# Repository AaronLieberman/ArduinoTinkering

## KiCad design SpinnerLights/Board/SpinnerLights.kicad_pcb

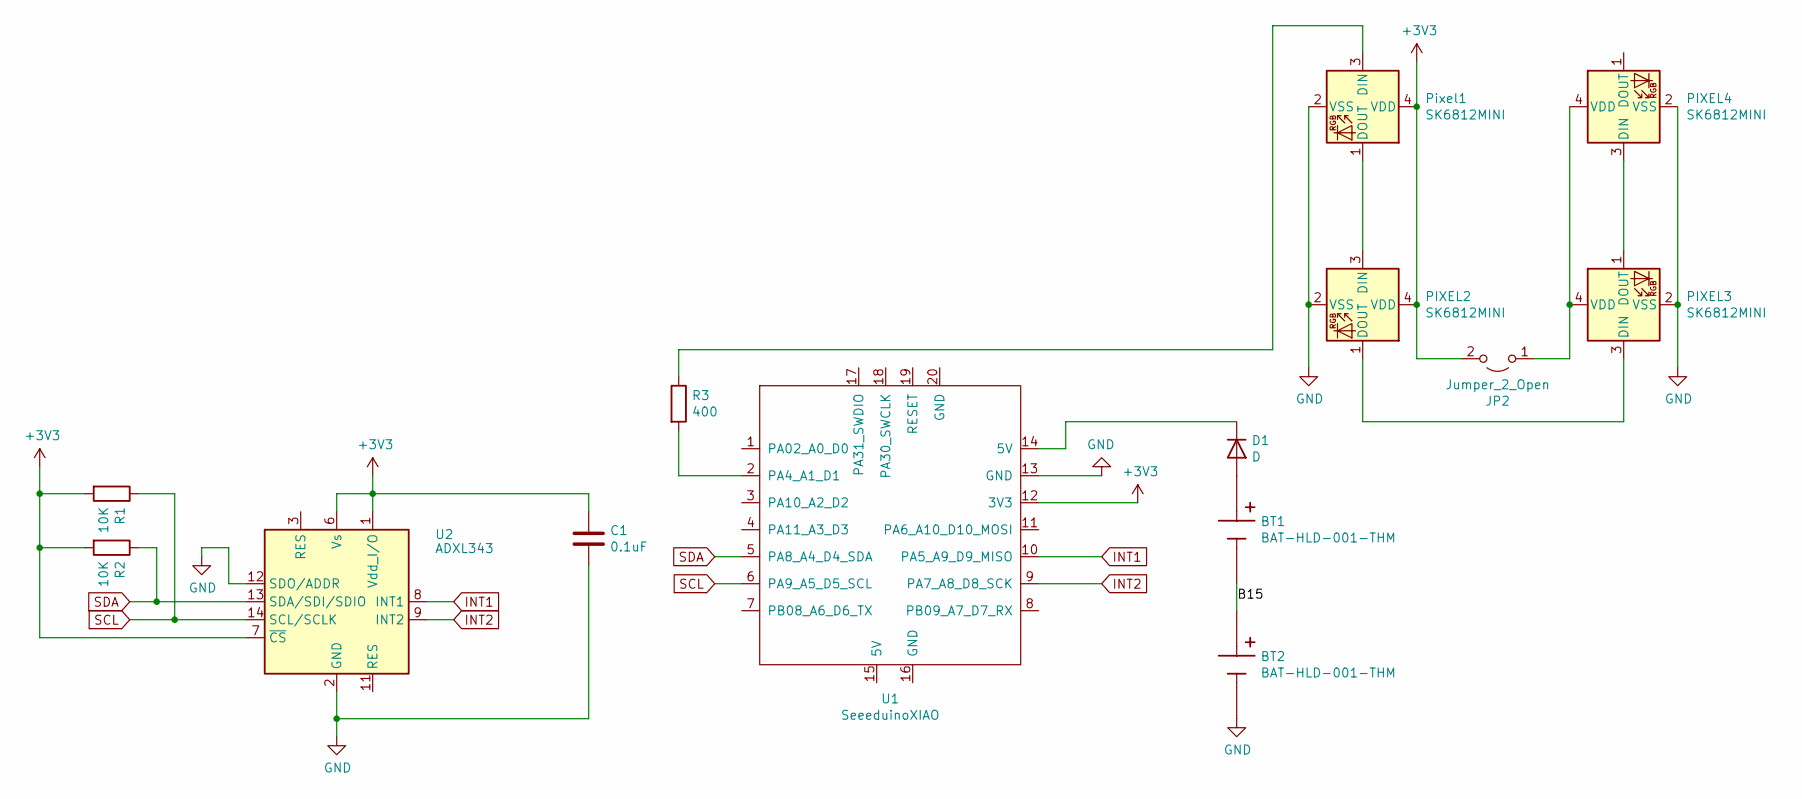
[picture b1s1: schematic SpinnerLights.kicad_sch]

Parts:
BT1, BT2: BAT-HLD-001-THM; BAT_BAT-HLD-001-THM; PARTREV C
C1: 0.1uF; C_0805_2012Metric
D1: D; D_SOD-323
JP2: Jumper_2_Open; SolderJumper-2_P1.3mm_Open_RoundedPad1.0x1.5mm
PIXEL2, PIXEL3, PIXEL4: SK6812MINI; LED_SK6812MINI_PLCC4_3.5x3.5mm_P1.75mm
Pixel1: SK6812MINI; LED_SK6812MINI_PLCC4_3.5x3.5mm_P1.75mm
R1, R2: 10K; R_0805_2012Metric_Pad1.20x1.40mm_HandSolder
R3: 400; R_0805_2012Metric_Pad1.20x1.40mm_HandSolder
U1: SeeeduinoXIAO; Seeeduino XIAO-MOUDLE14P-2.54-21X17.8MM
U2: ADXL343; LGA-14_3x5mm_P0.8mm_LayoutBorder1x6y

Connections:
+3V3: C1.1, JP2.2 (B), PIXEL2.4 (VDD), Pixel1.4 (VDD), R1.2, R2.2, U1.12 (3V3), U2.1 (Vdd_I/O), U2.6 (Vs), U2.7 (~CS)
/B15: BT1.N, BT2.P1, BT2.P2, BT2.P3, BT2.P4
GND: BT2.N, C1.2, PIXEL2.2 (VSS), PIXEL3.2 (VSS), PIXEL4.2 (VSS), Pixel1.2 (VSS), U1.13 (GND), U2.2 (GND), U2.4 (GND), U2.5 (GND), U2.12 (SDO/ADDR)
INT1: U1.10 (PA5_A9_D9_MISO), U2.8 (INT1)
INT2: U1.9 (PA7_A8_D8_SCK), U2.9 (INT2)
unnamed: BT1.P1, BT1.P2, BT1.P3, BT1.P4, D1.2 (A)
unnamed: D1.1 (K), U1.14 (5V)
unnamed: JP2.1 (A), PIXEL3.4 (VDD), PIXEL4.4 (VDD)
unnamed: PIXEL2.1 (DOUT), PIXEL3.3 (DIN)
unnamed: PIXEL2.3 (DIN), Pixel1.1 (DOUT)
unnamed: PIXEL3.1 (DOUT), PIXEL4.3 (DIN)
unnamed: Pixel1.3 (DIN), R3.1
unnamed: R3.2, U1.2 (PA4_A1_D1)
SCL: R1.1, U1.6 (PA9_A5_D5_SCL), U2.14 (SCL/SCLK)
SDA: R2.1, U1.5 (PA8_A4_D4_SDA), U2.13 (SDA/SDI/SDIO)

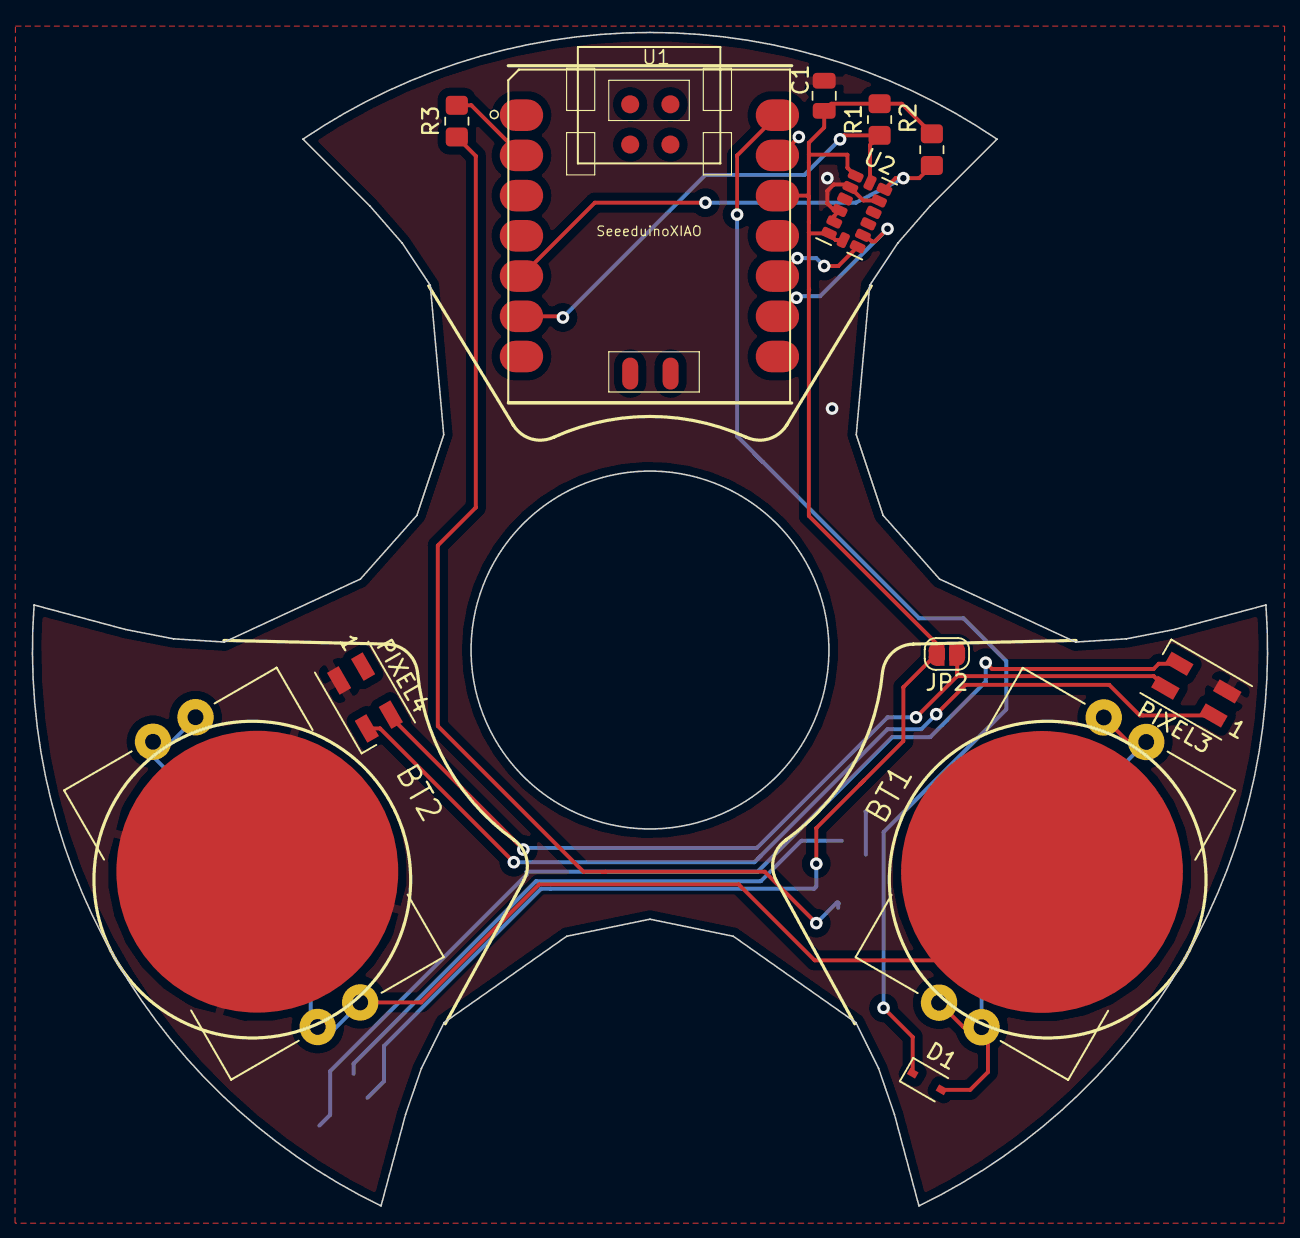
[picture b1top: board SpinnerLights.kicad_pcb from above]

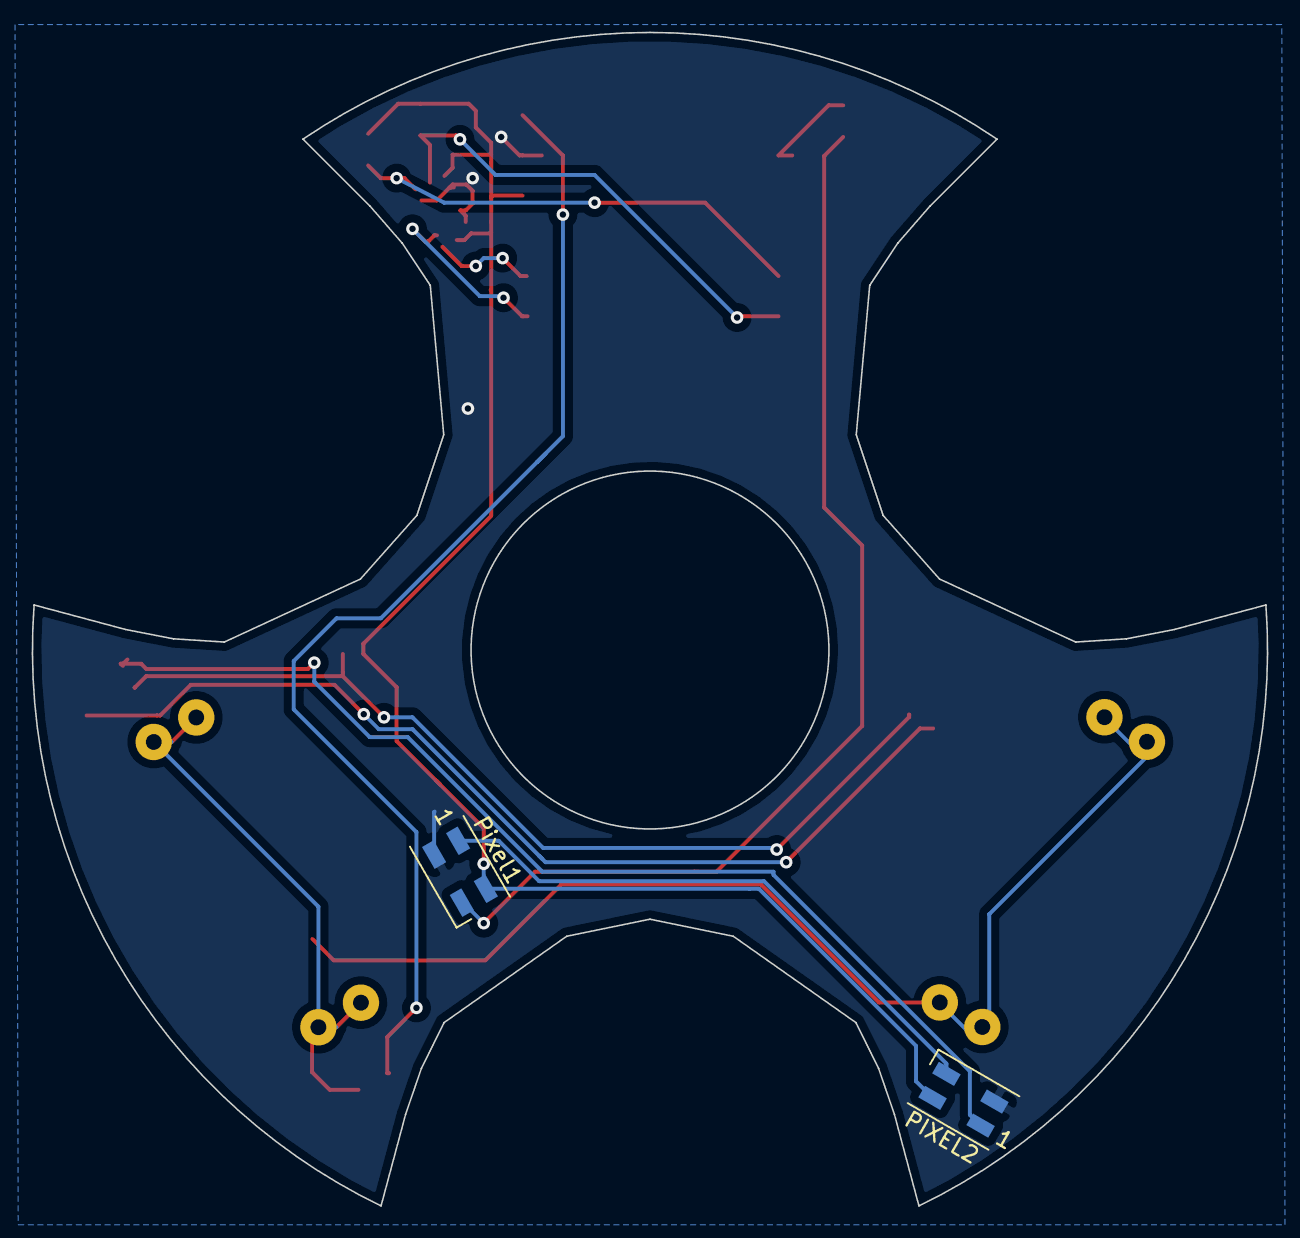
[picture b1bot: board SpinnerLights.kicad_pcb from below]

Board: 2 copper layers, 78.0 x 74.1 mm, 14 parts (2 on the bottom side), 15 nets.

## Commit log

2015-08-01 Added Temperature
2015-08-01 Added LedDisplay
2015-08-16 updates for new board layout, wip debugging stuff
2015-08-16 initial temperaturedisplay checkin
2015-08-16 minor cleanup and rename of variables
2015-08-17 Getting updated to the final layout of the trinket pro board. Extract various classes out to make TemperatureDisplay.
2015-08-17 Initial check-in of Thermostat by copying Temperatore
2015-08-17 V1 complete!
2016-01-10 led display no longer flickers! interrupts ftw
2016-01-10 tiny bit of code cleanup
2016-01-26 initial soundfabric checkin. controls the hue of several neopixels
2016-01-27 up to 7 pixels, add brightness wave
2016-01-28 whitespace fix
2016-01-28 add hue shift graph jpg for later reference
2016-01-29 mic controls a led strand
2016-01-30 continuous brightness based on volume
2016-01-30 Split out NeoPixelHue to it's own directory
2016-01-30 Add gain and log scale. It's working! Mic is picking up the sound and displaying it on the pixels.
2016-01-31 FHT Test
2016-01-31 getting slightly closer to fht but its still not working
2016-02-01 add .gitignore
2016-02-01 fftvisualizer windows app
2016-02-01 cleanup fftvisualizer code
2016-02-01 Visualization achievied!
2016-02-01 FhtToSerialTest app
2016-04-07 Add FFTVisualizer sketch and C# serial over USB app
2016-04-07 Revert "Add FFTVisualizer sketch and C# serial over USB app"
    This reverts commit 1848aa800e20f29074f41e0ccba744a692173c60.
2016-04-07 improvements to FFTVisualizer
2016-04-09 add micserial and visualizer
2016-05-04 FFTTest Python app, trying to figure out how FFT works.
2016-05-04 add .vc.db (python related VS file?) to .gitignore
2016-05-08 make data path relative
2016-05-30 working spectrum analyzer
2016-05-30 plays the right number of samples/s
2016-05-30 remove some commented out code
2016-06-02 add python version file
2016-06-02 make a copies of ffttest2.py for win and pi
2016-06-03 update FFTTest2-pi to use curses correctly
2016-06-04 add draft of alssound
2016-06-04 draft of using alsaudio
2016-06-04 add accidentally removed curses stuff back in
2016-10-09 fix NeoPixelHue delay
2016-10-09 fix temperature, should be targetting 150
2016-10-09 Halloween lights project
2017-01-06 Simple Fireflies blinking lights sketch
2017-01-06 Simple sketch to blink neopixels for halloween
2017-01-08 7 neopixel fireflies
2017-01-08 add lifetime scaling via pot
2017-01-22 Light detector using LEDs
2017-01-22 Fireflies - at least one LED is always on
2017-01-22 rename loop to tick
2017-01-22 Add some comments on how to use, rename some vars
2017-01-22 - Re-add loop, was inadvertently removed - Add second pixel strand, currently only has one pixel in it
2017-02-16 update fireflies to use fairy lights
2018-04-10 random changes from who knows when
2018-04-10 circuit playground express docs
2018-06-09 Get up and running in VS Code. Files for Trinket M0.
2018-06-09 Add ShelfLights.ino
2018-06-09 clang format
2018-12-30 remove .vscode dir from repo
2018-12-30 final version for shelflights
2019-01-02 Initial RobotController app
2019-01-02 Update to package references, switch to Addle version of Core and WPF
2019-01-02 Add message received UI
2019-01-04 RobotControl w/ SerialPort replacement class that actually works (unlike the built in .NET one)
2019-01-06 Robot controller works!
2019-01-19 minor tweak
2019-02-14 messing with robot control via python and arduino
2019-02-16 start code to load animations.txt
2019-03-13 animation playback software
2019-03-14 per-servo config
2019-03-27 Animations finally working!
2019-04-11 LED buttons work! - Fix stlhelper to work for multiple files
2019-04-13 buttons to trigger animations
2019-05-05 initial OzControlPanel check in + try out scheduler library
2019-05-08 v1.0
2019-05-21 final oz
2019-06-19 minor adjustments to enable_servos define
2019-06-19 New animationData
2019-06-19 robot blender file
2019-07-31 Initial MalStaff
2019-08-03 glow and blinking green
2019-08-11 might be the final version of the staff
2019-09-28 add clang format for RobotAnimations
2019-09-28 Clang format RobotAnimations
2019-09-28 Extract out ServoController
2019-09-29 doesn't crash anymore, ready for dev again
2019-09-29 Extract out AnimationPlayer
2019-09-29 setup mode works
2019-09-29 wave working
2019-09-30 animations work
2019-09-30 Fixed data to be correctly const so it lives in flash instead of sram
2019-09-30 update blend files
2019-10-04 Pretty much final software
2019-10-04 update animations
2019-10-04 more work on the macerena
2019-10-04 maybe done now?
2019-10-04 macerena blend file
2019-10-04 adjust idle timeout
2019-12-22 VolumeControl
2019-12-22 comment
2019-12-23 better button support
2019-12-23 switch encoder to use polling instead of interrupts
2019-12-23 simplify encoder logic
2019-12-24 move where serial is initialized
2020-07-26 PrusaLights
2020-07-26 VS Code workspace
2020-09-05 Update default clang format to use attached braces
2020-09-05 more clang format updates
2020-09-05 Beginning of HyperFig code
2020-09-05 Add some of the .vscode files to source control
2020-09-07 HyperFig code complete
2021-08-23 HyperFig: some progress towards multiple buttons on one pin
    also some line endings fixing i think
2021-08-23 Initial SpinnerLights (copied from HyperFig)
2021-08-23 SpinnerLights controls NeoPixels
2021-08-24 SpinnerLights: uses accelerometer on PyBadge to control neopixels
2021-08-28 Filter accel values, a bit of cleanup
2021-08-28 A little header cleanup
2021-10-12 Basic spinner works
2021-10-12 clangformat: fix pointer alignment
2021-10-12 Move SpinnerLights to subdir
2021-10-12 SpinnerLights: Initial KiCad setup
2021-10-13 WIP on SpinnerLights board
2021-10-13 SpinnerLights: Initial netlist and schematics
2021-10-13 SpinnerLights: Initial board generation
2021-10-13 SpinnerLights: More progress on board layout
2021-10-14 SpinnerLights: started laying down wires
2021-10-14 SpinnerLights: Almost complete routing
2021-10-14 SpinnerLights: Initial version first pass complete
2021-10-14 SpinnerLights: Fix I2C interface pins
2021-10-14 SpinnerLights: minor tweaks to ground plane
2021-10-15 SpinnerLights: Rename a couple nets
2021-10-15 SpinnerLights: Fix symbols for NeoPixels
2021-10-15 SpinnerLights: move a couple of components around to give more space
2021-10-16 SpinnerLights: Minor tweaks to placement and routing
2021-10-16 SpinnerLights: Remove files that don't belong in source control
2021-10-16 SpinnerLights: .gitignore file
2022-01-09 Upgrade kicad files to v6
2022-05-18 Get SpinnerLights to build again by moving to directory named SpinnerLights
2022-05-18 SpinnerLights: Get working with PCB version and ADXL345
2022-05-20 PCB v1 complete
2022-09-22 SpinnerLights minor update
2022-09-22 VolumeControl v3
2023-01-10 Turn off test serial for volumecontrol
2023-01-11 IOExpanderTest
2023-01-11 IOExpanderTest: both read and write
2024-07-12 Split IOExpanderTest into read and write versions
2024-07-12 IOExpanderTestRead tests ASD keys
2024-08-03 just some formatting
2024-08-05 Switch to row output, col input
2024-08-05 add right side
2024-08-05 scans rows to support all keys, both left and right
2024-08-10 some clean up so that hid-project library is compatible with ioexpandertestread.ino
2024-08-10 Initial KeyboardWingsv2.ino based on IOExpanderTestRead.ino
2024-08-11 Start sketching out the scanning code
2024-08-14 Scan implementation and optimization
2024-08-15 Scanning, key up, key down works
2024-08-15 keyboard layout (works?!)
2024-09-06 Add in some old SimpleLights code that was on a laptop but never got committed
2024-09-06 If one IO expander fails to init, put it offline
2024-09-06 Couple keyscanner features such as disable keypresses for debugging
2024-09-06 Slight keysseen improvement
2024-09-07 Better display for keysseen
2024-09-08 Refactor keysseen code a bit to avoid duplication
2024-09-08 FastScan initial impl
2024-09-08 Split keyscanner to left and right halves. WIP
2024-09-09 FastScan works. Not sure about its perf yet
2024-09-09 Remove debouncer and latchbutton since they weren't being used
2024-09-09 A couple more fixes to fastscan
2024-09-09 Only process the side(s) that fastscan returned true for
2024-09-10 Minor refactor to processside
2024-09-12 fix trivial bug
2024-09-14 remove extraneous comments
2024-09-15 Fix some bugs with FastScan
2024-09-15 Media keys
2024-09-16 Switch active/inactive to be based on whether key is down vs. changed. Add some timers
2024-09-21 Add special key combos (press app key 3 times quickly => win+L)
2024-12-25 Add support for ctrl+volume for switching tracks by refactoring hotkey management
2024-12-26 Encoder works much better, uses interrupts, scales appropriately
